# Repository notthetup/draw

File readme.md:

# Draw

INA260 based voltage and current __draw__ measurement board.

This is a INA260 based board for measuring voltage and current draw (with builtin shunt) and output over USB (CDC).

## V2.0 - Under development.

The idea with v2 is to use an ESP32-C3. It's a cheap micro-controller. It has WiFi which may be handy, and it has USB.

While it's possible to use a ESP32-C3 module like the [ESP32-C3-WROOM-02U-N4](https://www.digikey.sg/en/products/detail/espressif-systems/ESP32-C3-WROOM-02U-N4/15222540), one would have to deal with powering the module from USB (5V), the reset circuitry, and the USB-C connector. It's much simpler to use the [Seeed Studio XIAO ESP32C3](https://wiki.seeedstudio.com/XIAO_ESP32C3_Getting_Started/) which has all those components built in for a very low price.

### Features

- Current/Voltage/Power measurement
- Configurable over USB/WiF
    - Sensor gain
    - Sensor offset ??
    - Update rate
    - Averaging modes
- Optionally Tie ground to USB ground ??
- Optionally connect sensor VIN to INA260 VDD
- VIN, GND, VOUT on terminal block connector
- Configurable alerts values and output
- External power supply (5V)
- SPI pulled out for display (optional)
- pulled out IO pins to control/trigger/sense activity

### General price breakdown

- Seeed Studio XIAO ESP32C3 - ~[US$4.99](https://www.seeedstudio.com/Seeed-XIAO-ESP32C3-p-5431.html?queryID=015416e491c3db2e8304a974f8ab6ce7&objectID=5431&indexName=bazaar_retailer_products)
- INA260 - ~[US$6.38](https://www.digikey.com/en/products/detail/texas-instruments/INA260AIPW/6589219)
- Other components - ~US$10.00
**Total** - ~US$21.37

## V1.0

Documented [on this tag](https://github.com/notthetup/draw/tree/v1.0)

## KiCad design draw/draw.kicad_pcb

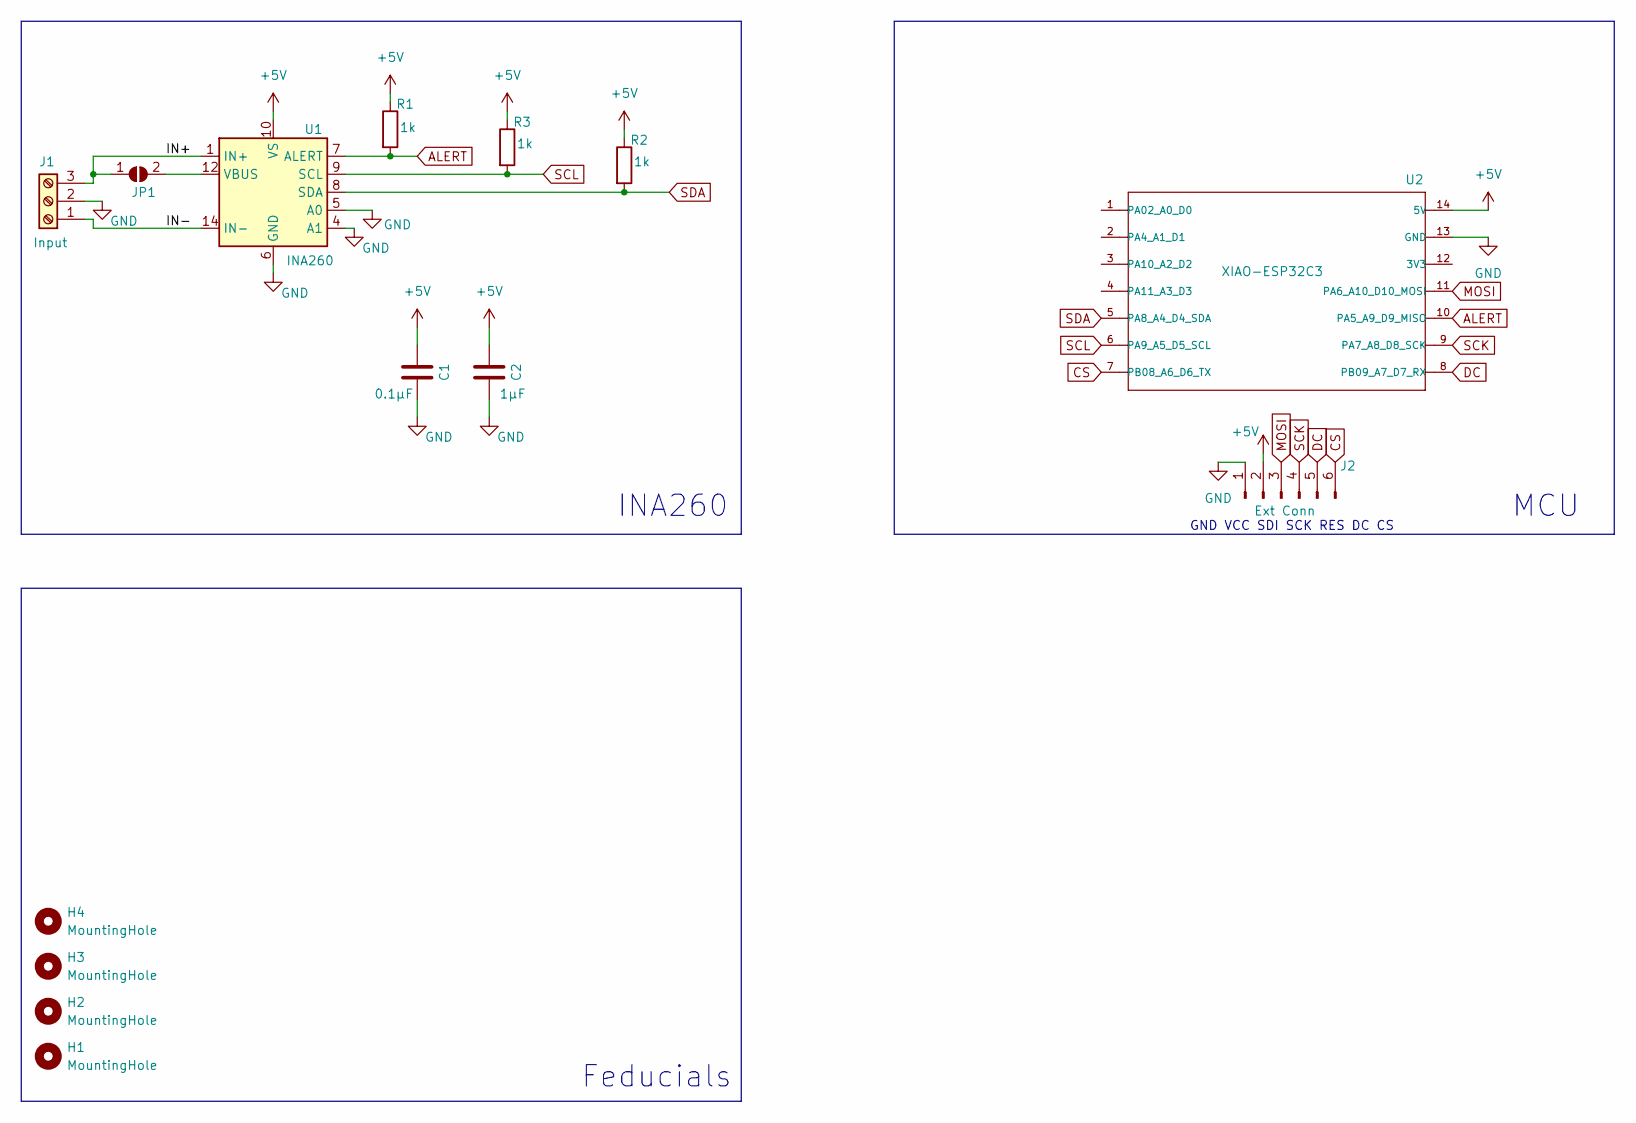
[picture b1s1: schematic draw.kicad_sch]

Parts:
C1: 0.1µF; C_0805_2012Metric_Pad1.18x1.45mm_HandSolder
C2: 1µF; C_0805_2012Metric_Pad1.18x1.45mm_HandSolder
H1, H2, H3, H4: MountingHole; MountingHole_2.5mm
J1: Input; TerminalBlock_Phoenix_MPT-0,5-3-2.54_1x03_P2.54mm_Horizontal
J2: Ext Conn; PinHeader_1x06_P2.54mm_Vertical
JP1: SolderJumper_2_Open; SolderJumper-2_P1.3mm_Open_TrianglePad1.0x1.5mm
R1, R2, R3: 1k; R_0805_2012Metric_Pad1.20x1.40mm_HandSolder
U1: INA260; TSSOP-16_4.4x5mm_P0.65mm
U2: XIAO-ESP32C3; MOUDLE14P-SMD-2.54-21X17.8MM

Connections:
+5V: C1.1, C2.1, J2.2, R1.1, R2.1, R3.1, U1.10 (VS), U2.14 (5V)
/IN+: J1.3, JP1.1 (A), U1.1 (IN+), U1.2 (IN+), U1.3 (IN+)
/IN-: J1.1, U1.14 (IN-), U1.15 (IN-), U1.16 (IN-)
ALERT: R1.2, U1.7 (ALERT), U2.10 (PA5_A9_D9_MISO)
CS: J2.6, U2.7 (PB08_A6_D6_TX)
DC: J2.5, U2.8 (PB09_A7_D7_RX)
GND: C1.2, C2.2, J1.2, J2.1, U1.4 (A1), U1.5 (A0), U1.6 (GND), U1.11 (GND), U2.13 (GND)
MOSI: J2.3, U2.11 (PA6_A10_D10_MOSI)
unnamed: JP1.2 (B), U1.12 (VBUS)
SCK: J2.4, U2.9 (PA7_A8_D8_SCK)
SCL: R3.2, U1.9 (SCL), U2.6 (PA9_A5_D5_SCL)
SDA: R2.2, U1.8 (SDA), U2.5 (PA8_A4_D4_SDA)

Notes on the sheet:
Feducials
INA260
GND VCC SDI SCK RES DC CS
MCU

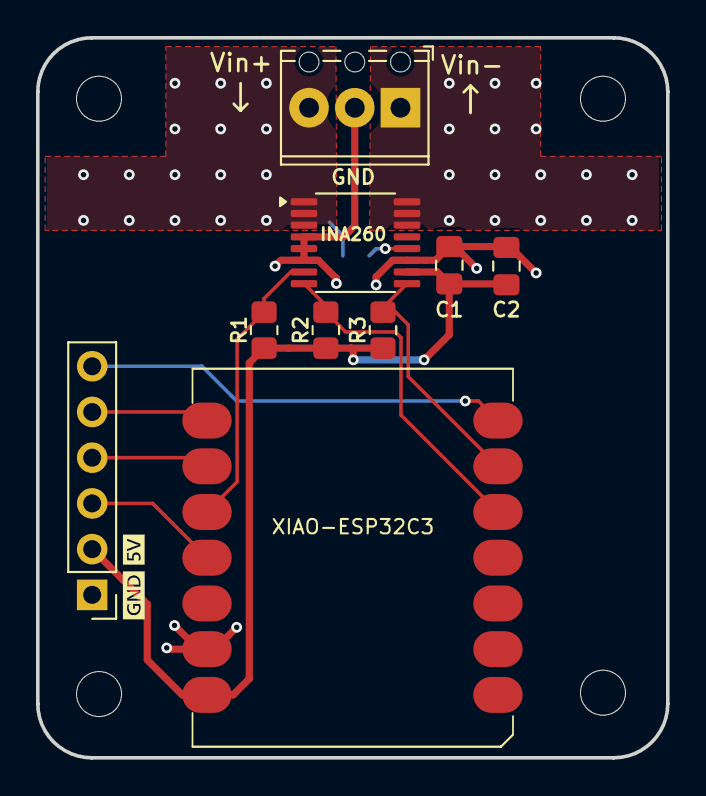
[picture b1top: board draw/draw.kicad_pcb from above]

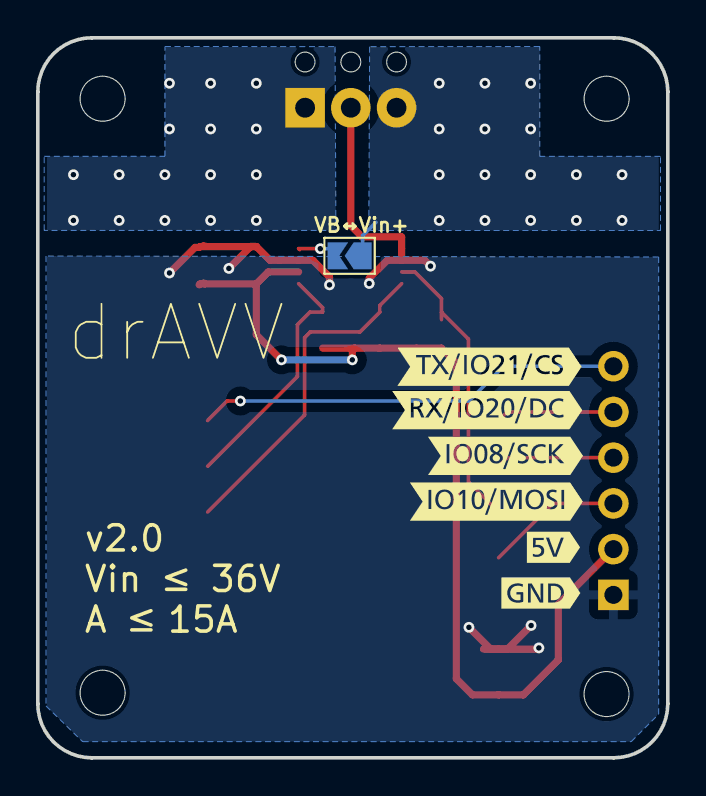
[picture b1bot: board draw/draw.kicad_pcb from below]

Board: 2 copper layers, 35.0 x 40.0 mm, 22 parts (7 on the bottom side), 12 nets.

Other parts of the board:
kibuzzard-65F449CA: G***; kibuzzard-65F449CA
kibuzzard-65F2691B: G***; kibuzzard-65F2691B
kibuzzard-65F4499A: G***; kibuzzard-65F4499A
kibuzzard-65F26913: G***; kibuzzard-65F26913
kibuzzard-65F26926: G***; kibuzzard-65F26926
kibuzzard-65F26930: G***; kibuzzard-65F26930
kibuzzard-65F26950: G***; kibuzzard-65F26950
kibuzzard-65F26955: G***; kibuzzard-65F26955

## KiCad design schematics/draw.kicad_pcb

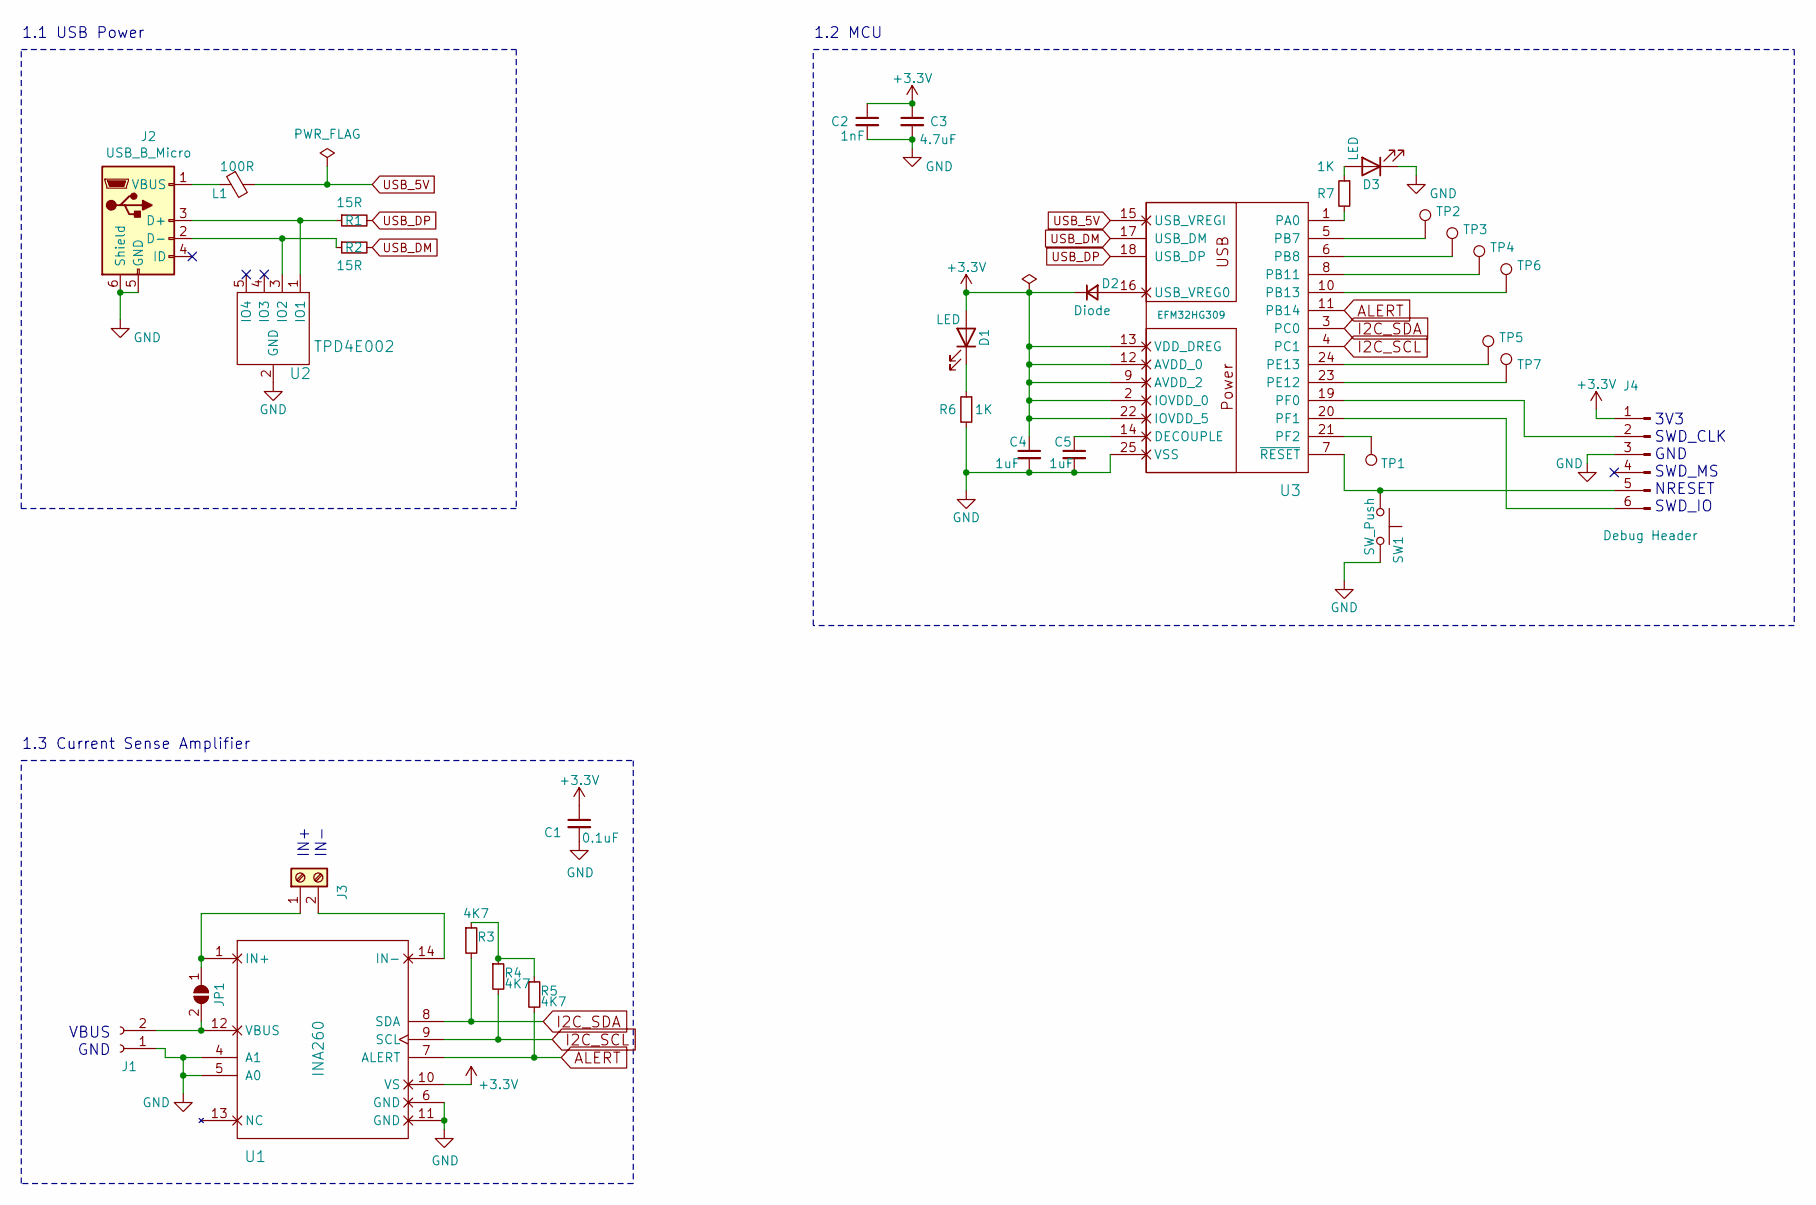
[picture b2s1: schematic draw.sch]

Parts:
C1: 0.1uF; C_0805_2012Metric_Pad1.15x1.40mm_HandSolder
C2: 1nF; C_0805_2012Metric_Pad1.15x1.40mm_HandSolder
C3: 4.7uF; C_0805_2012Metric_Pad1.15x1.40mm_HandSolder
C4, C5: 1uF; C_0805_2012Metric_Pad1.15x1.40mm_HandSolder
D1, D3: LED; LED_0805_2012Metric_Pad1.15x1.40mm_HandSolder
D2: Diode; D_0805_2012Metric_Pad1.15x1.40mm_HandSolder
J1: Conn_01x02_Female; PinHeader_1x02_P1.00mm_Vertical
J2: USB_B_Micro; USB_Micro-B_Amphenol_10103594-0001LF_Horizontal
J3: Screw_Terminal_01x02; TerminalBlock_MetzConnect_Type086_RT03402HBLC_1x02_P3.81mm_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
J4: Debug Header; PinSocket_1x06_P2.54mm_Vertical
JP1: Jumper; SolderJumper-2_P1.3mm_Open_RoundedPad1.0x1.5mm
L1: 100R; L_0805_2012Metric_Pad1.15x1.40mm_HandSolder
R1, R2: 15R; R_0805_2012Metric_Pad1.15x1.40mm_HandSolder
R3, R4, R5: 4K7; R_0805_2012Metric_Pad1.15x1.40mm_HandSolder
R6, R7: 1K; R_0805_2012Metric_Pad1.15x1.40mm_HandSolder
SW1: SW_Push; Tact
TP1, TP2, TP3, TP4, TP5, TP6, TP7: TestPoint; TestPoint_Pad_2.0x2.0mm
U1: INA260; TSSOP-16_4.4x5mm_P0.65mm
U2: TPD4E002; SOT-553
U3: EFM32HG309; QFN-24-1EP_5x5mm_P0.65mm_EP3.6x3.6mm

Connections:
+3V3: C1.1, C2.1, C3.1, C4.1, D1.2 (A), D2.1 (K), J4.1, U1.10 (VS), U3.2 (IOVDD_0), U3.9 (AVDD_2), U3.12 (AVDD_0), U3.13 (VDD_DREG), U3.22 (IOVDD_5)
ALERT: R5.2, U1.7 (ALERT), U3.11 (PB14)
GND: C1.2, C2.2, C3.2, C4.2, C5.2, D3.1 (K), J1.1, J2.5 (GND), J2.6 (Shield), J4.3, R6.2, SW1.2, U1.4 (A1), U1.5 (A0), U1.6 (GND), U1.11 (GND), U2.2 (GND), U3.25 (VSS)
I2C_SCL: R4.2, U1.9 (SCL), U3.4 (PC1)
I2C_SDA: R3.2, U1.8 (SDA), U3.3 (PC0)
unnamed: C5.1, U3.14 (DECOUPLE)
unnamed: D1.1 (K), R6.1
unnamed: D2.2 (A), U3.16 (USB_VREG0)
unnamed: D3.2 (A), R7.1
unnamed: J1.2, JP1.2 (B), U1.12 (VBUS)
unnamed: J2.1 (VBUS), L1.1
unnamed: J2.2 (D-), R2.1, U2.3 (IO2)
unnamed: J2.3 (D+), R1.1, U2.1 (IO1)
unnamed: J3.1, JP1.1 (A), U1.1 (IN+), U1.2 (IN+), U1.3 (IN+)
unnamed: J3.2, U1.14 (IN-), U1.15 (IN-), U1.16 (IN-)
unnamed: J4.2, U3.19 (PF0)
unnamed: J4.5, SW1.1, U3.7 (~RESET)
unnamed: J4.6, U3.20 (PF1)
unnamed: R3.1, R4.1, R5.1
unnamed: R7.2, U3.1 (PA0)
unnamed: TP1.1, U3.21 (PF2)
unnamed: TP2.1, U3.5 (PB7)
unnamed: TP3.1, U3.6 (PB8)
unnamed: TP4.1, U3.8 (PB11)
unnamed: TP5.1, U3.24 (PE13)
unnamed: TP6.1, U3.10 (PB13)
unnamed: TP7.1, U3.23 (PE12)
USB_5V: L1.2, U3.15 (USB_VREGI)
USB_DM: R2.2, U3.17 (USB_DM)
USB_DP: R1.2, U3.18 (USB_DP)

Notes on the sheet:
3V3 SWD_CLK GND SWD_MS NRESET SWD_IO
1.1 USB Power
1.2 MCU
1.3 Current Sense Amplifier
IN+ IN-
VBUS GND

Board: 2 copper layers, 32 parts (0 on the bottom side), 30 nets, no tracks yet.

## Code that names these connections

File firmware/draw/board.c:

#include "board.h"

void board_init() {
  /*Init peripheral clocks*/

  /* Enable USHFRCO Oscillator */
  cmu_osc_on(USHFRCO);
  cmu_wait_for_osc_ready(USHFRCO);

  /* Use USHFRCO as main HFCLK */
  cmu_set_hfclk_source(USHFRCO);
  cmu_osc_off(CMU_OSCENCMD);

  /* Enable GPIO and I2C0 clocks */
  cmu_periph_clock_enable(CMU_GPIO);
  cmu_periph_clock_enable(CMU_I2C0);

  /*Setup Pins for I2C*/
  gpio_mode_setup(GPIOC, GPIO_MODE_WIRED_AND, 0); // PC0 - I2C0-SDA
  gpio_mode_setup(GPIOC, GPIO_MODE_WIRED_AND, 1); // PC1 - I2C0-SCL

  gpio_mode_setup(GPIOB, GPIO_MODE_INPUT, 11); // PB11 - Alert

  gpio_set(GPIOC,0);
  gpio_set(GPIOC,1);
}

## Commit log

2017-01-18 added references
2017-01-20 initial schematics
2017-01-20 changed to EFM32HG309
2017-01-20 split into 2 sheets + drc
2017-01-22 added pullups for I2C and alert
2017-01-22 added links to datasheets
2017-01-22 added moar decoulping caps
2017-01-22 added footprint for switch
2017-01-30 first layout
2017-02-05 second layout
2017-02-05 third layout, passes drc
2017-02-05 added gerbers
2017-02-07 updated pdf
2017-02-07 moved things around and layout pdf
2017-02-07 added logo and url silkscreen
2017-02-12 updated gerbers
2017-02-12 removed zipped file archive
2017-02-22 added bom tracking
2017-03-14 fixed the issue with the power pads for INA260
2017-03-14 updated silkscreen bumped version
2017-03-31 fixed the footprint for button
2017-04-07 added openocd flashing conf and tomu usb bootloader
2017-04-09 added firmware and ignore tomu-examples
2017-04-09 added basic firmware based on tomu
2017-05-07 basic working firmware with i2c output over uart
2017-05-10 added simple usb enum
2017-05-14 added stdio debug, an0042 bl, update linker flash check
2017-05-14 made stdio redirect to work
2017-05-14 added retargetserial sample
2017-05-14 cleaned up firmware code
2017-05-14 attempt at USB cdc: doesn't work
2019-03-23 rescuing efm32
2019-03-23 moving to kicad5
2019-03-23 updated to work in kicad 5.1
2019-03-23 removing all the rescued parts
2019-03-24 removed tomu samples
2019-07-27 moved to new firmware from tomu-samples
2019-07-27 added submodule for libopencm3
2019-08-11 initial commit of libopencm3
2019-08-17 working i2c and printf code
2019-08-17 basic working version with start command
2019-08-17 split out code into differeny files
2019-08-18 cleanup
2019-08-18 added voltage/current getter
2019-08-18 semi working code for reading voltage and power
2019-08-18 barely working power readout on USB
2019-12-13 fixed issues in reading i2c, works well now.
2020-01-12 updated libopencm3 apis to make i2c work
2020-01-12 support for getting configs
2020-01-12 moved to 400kHz I2C
2020-01-27 basic command parser
2020-04-19 code cleanup
2020-07-12 fix(schematic): updated resistor value of LED current limit resistor to 1K
2020-07-12 debug
2020-07-12 fixed typo
2020-07-12 basic command infrastcture
2020-07-12 setup for alert interrupts
2020-08-01 testing cmu settings WIP
2020-08-09 v2 schematic
2020-08-09 changed resistors to 4K7
2020-08-15 added VBUS and GND Power headers
2020-09-08 updating footprint assignment
2024-03-02 cleaning up for v2
2024-03-02 setting up PCB for v2
2024-03-15 implemented schematic and pcb for draw v2
2024-03-17 added ibom
2024-03-17 removed lck
